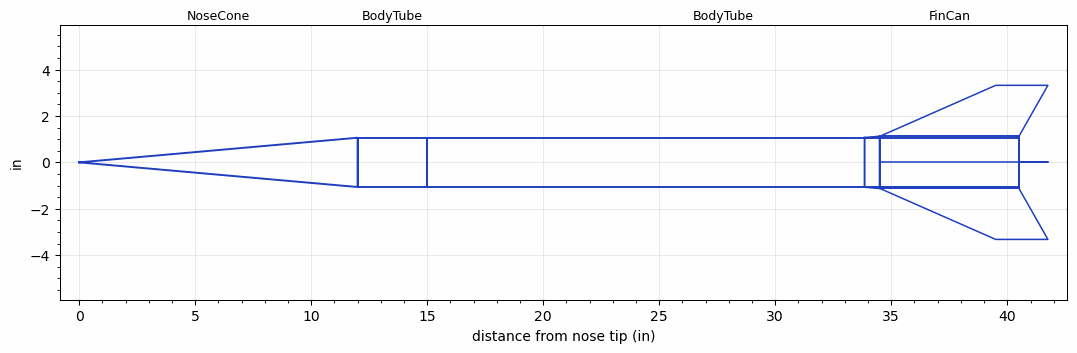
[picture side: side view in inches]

<RASAeroDocument>
 <FileVersion>2</FileVersion>
 <RocketDesign>
  <NoseCone>
   <Length>12</Length>
   <Diameter>2.125</Diameter>
   <Shape>Conical</Shape>
   <BluntRadius>0.0625</BluntRadius>
   <Location>0</Location>
  </NoseCone>
  <BodyTube>
   <Length>3</Length>
   <Diameter>2.125</Diameter>
   <Location>12</Location>
  </BodyTube>
  <BodyTube>
   <Length>25.5</Length>
   <Diameter>2.125</Diameter>
   <Location>15</Location>
  </BodyTube>
  <FinCan>
   <Length>6</Length>
   <Diameter>2.24</Diameter>
   <InsideDiameter>2.125</InsideDiameter>
   <Location>40.5</Location>
   <ShoulderLength>0.65</ShoulderLength>
   <Offset>-6</Offset>
   <Fin>
    <Count>4</Count>
    <Chord>6</Chord>
    <Span>2.2</Span>
    <SweepDistance>5</SweepDistance>
    <TipChord>2.25</TipChord>
    <Thickness>0.177</Thickness>
    <LERadius>0.001</LERadius>
    <Location>6</Location>
    <AirfoilSection>Hexagonal</AirfoilSection>
    <FX1>0.83</FX1>
    <FX3>0.83</FX3>
   </Fin>
  </FinCan>
  <Surface>Rough Camouflage Paint</Surface>
  <ModifiedBarrowman>True</ModifiedBarrowman>
  <Turbulence>True</Turbulence>
  <UseBooster1>False</UseBooster1>
  <UseBooster2>False</UseBooster2>
 </RocketDesign>
 <LaunchSite>
  <Altitude>2000</Altitude>
  <Pressure>0</Pressure>
  <RodAngle>0</RodAngle>
  <RodLength>4</RodLength>
  <Temperature>74</Temperature>
  <WindSpeed>0</WindSpeed>
 </LaunchSite>
 <Recovery>
  <Altitude1>1000</Altitude1>
  <Altitude2>1000</Altitude2>
  <DeviceType1>None</DeviceType1>
  <DeviceType2>None</DeviceType2>
  <Event1>False</Event1>
  <Event2>False</Event2>
  <Size1>1</Size1>
  <Size2>1</Size2>
  <EventType1>None</EventType1>
  <EventType2>None</EventType2>
  <CD1>1.33</CD1>
  <CD2>1.33</CD2>
 </Recovery>
 <SimulationList>
  <Simulation>
   <SustainerEngine>K767  (MYA)</SustainerEngine>
   <SustainerLaunchWt>6.71</SustainerLaunchWt>
   <SustainerNozzleDiameter>1.9</SustainerNozzleDiameter>
   <SustainerCG>24.5</SustainerCG>
   <SustainerIgnitionDelay>0</SustainerIgnitionDelay>
   <Booster1SeparationDelay>0</Booster1SeparationDelay>
   <Booster1IgnitionDelay>0</Booster1IgnitionDelay>
   <IncludeBooster1>False</IncludeBooster1>
   <Booster2Delay>0</Booster2Delay>
   <IncludeBooster2>False</IncludeBooster2>
   <TimetoApogee>29.30058</TimetoApogee>
   <MaxAltitude>21826.94</MaxAltitude>
   <MaxVelocity>2737.756</MaxVelocity>
  </Simulation>
 </SimulationList>
</RASAeroDocument>
